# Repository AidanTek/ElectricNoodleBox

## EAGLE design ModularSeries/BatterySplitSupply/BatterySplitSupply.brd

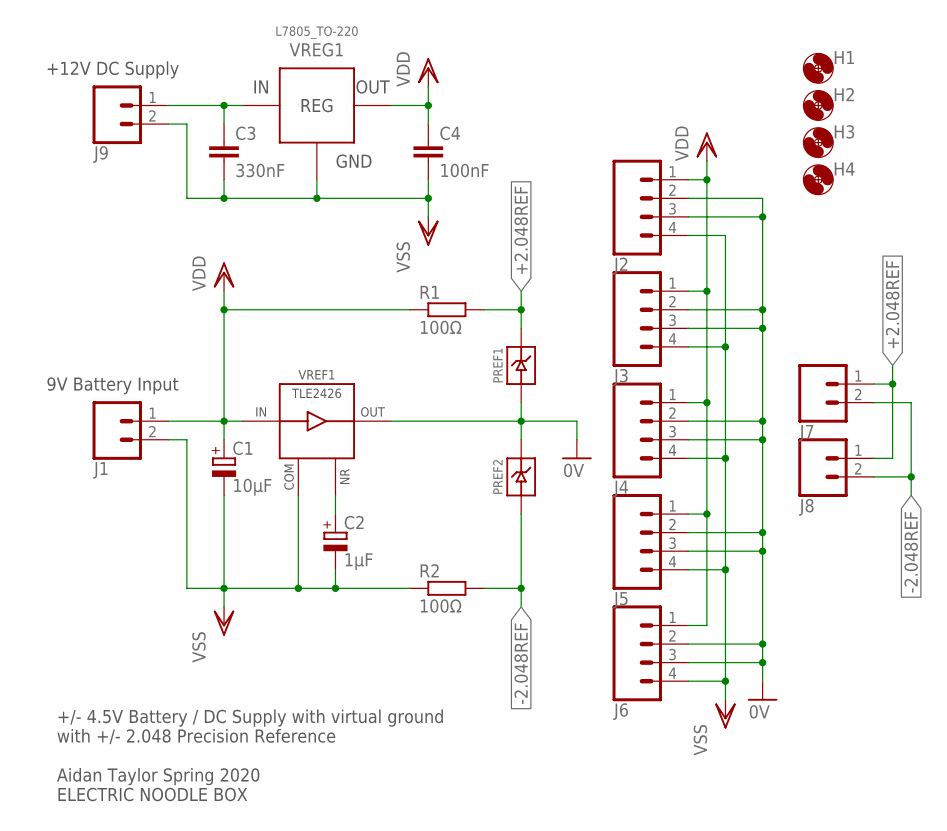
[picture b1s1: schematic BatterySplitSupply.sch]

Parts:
C1: 10µF; E2-5
C2: 1µF; E2-5
C3: 330nF; C050-025X075
C4: 100nF; C050-025X075
H1, H2, H3, H4: MOUNT-HOLE3.2; 3,2
J1, J7, J8, J9: 2XMOLEX; MOLEX-1X2
J2, J3, J4, J5, J6: 4XMOLEX; MOLEX-1X4
PREF1, PREF2: LM4040TH; TO-92
R1, R2: 100Ω; 0207/10
VREF1: TLE2426DIL; DIL08
VREG1: L7805_TO-220; TO220H

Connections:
0V: J2.2, J2.3, J3.2, J3.3, J4.2, J4.3, J5.2, J5.3, J6.2, J6.3, PREF1.3 (ANODE), PREF2.2 (CATHODE), VREF1.1 (OUTPUT)
+2.048REF: J7.1, J8.1, PREF1.2 (CATHODE), R1.2
-2.048REF: J7.2, J8.2, PREF2.3 (ANODE), R2.2
GND: C3.2, C4.2, J9.2, VREG1.2 (GND)
unnamed: C3.1, J9.1, VREG1.1 (VIN)
unnamed: C2.+, VREF1.8 (NR)
VDD: C1.+, C4.1, J1.1, J2.1, J3.1, J4.1, J5.1, J6.1, R1.1, VREF1.3 (INPUT), VREG1.3 (VOUT)
VSS: C1.-, C2.-, J1.2, J2.4, J3.4, J4.4, J5.4, J6.4, R2.1, VREF1.2 (COM)

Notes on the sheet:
+12V DC Supply
9V Battery Input
+/- 4.5V Battery / DC Supply with virtual ground with +/- 2.048 Precision Reference Aidan Taylor Spring 2020 ELECTRIC NOODLE BOX

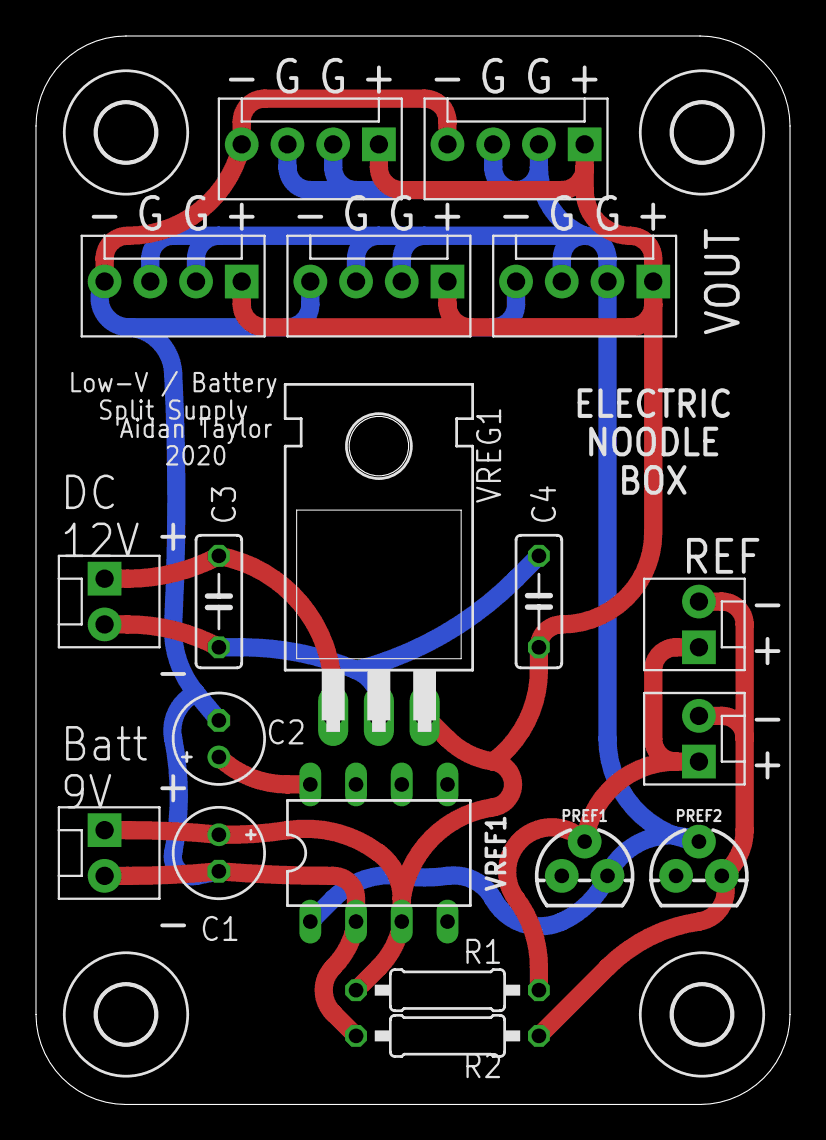
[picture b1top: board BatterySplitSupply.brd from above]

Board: 2 copper layers, 41.9 x 59.4 mm, 23 parts (0 on the bottom side), 8 nets.

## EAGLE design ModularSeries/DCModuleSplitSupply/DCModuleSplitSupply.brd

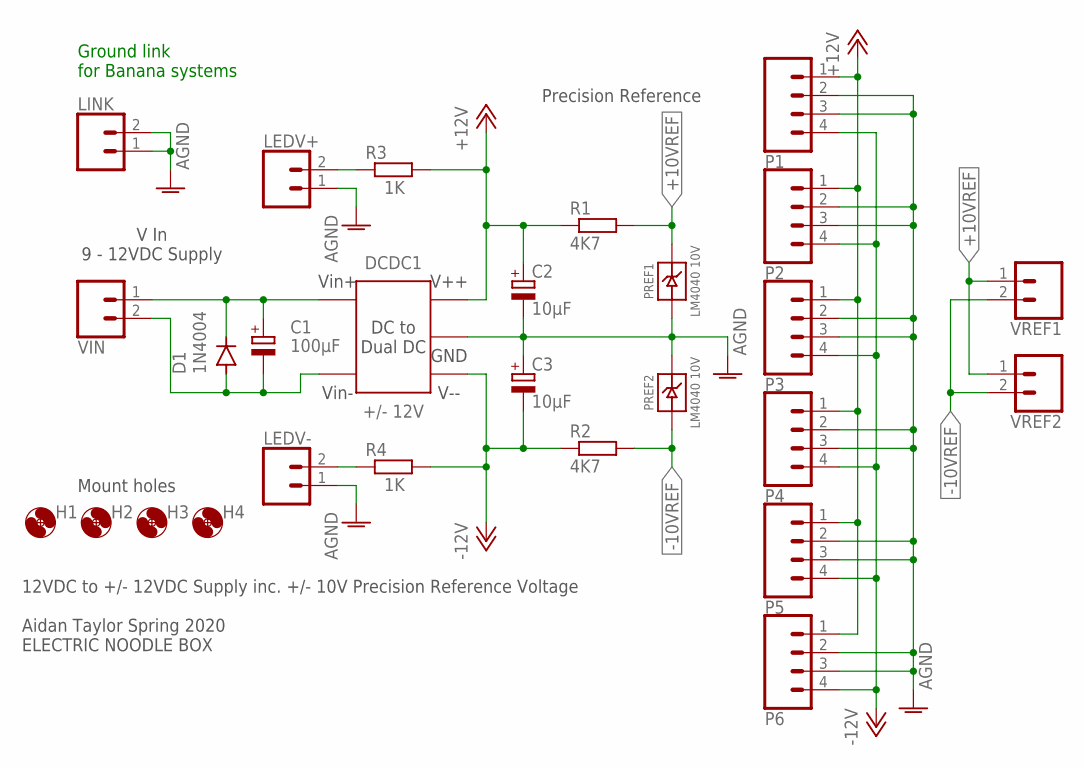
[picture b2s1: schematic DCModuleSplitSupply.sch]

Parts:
C1: 100µF; E2,5-6
C2, C3: 10µF; E2-5
D1: 1N4004; DO41-10
DCDC1: +/- 12V; VRA_ZP-6WR3_SERIES
H1, H2, H3, H4: MOUNT-HOLE3.2; 3,2
LEDV+: 2XWIREPAD; 1X02
LEDV-: 2XWIREPAD; 1X02
LINK: 2XWIREPAD; 1X02
P1, P2, P3, P4, P5, P6: 4XMOLEX; MOLEX-1X4
PREF1, PREF2: LM4040 10V; TO-92
R1, R2: 4K7; 0207/10
R3, R4: 1K; 0207/10
VIN: 2XMOLEX; MOLEX-1X2
VREF1, VREF2: 2XMOLEX; MOLEX-1X2

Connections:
+10VREF: PREF1.2 (CATHODE), R1.2, VREF1.1, VREF2.1
+12V: C2.+, DCDC1.VOUT+, P1.1, P2.1, P3.1, P4.1, P5.1, P6.1, R1.1, R3.2
-10VREF: PREF2.3 (ANODE), R2.2, VREF1.2, VREF2.2
-12V: C3.-, DCDC1.VOUT-, P1.4, P2.4, P3.4, P4.4, P5.4, P6.4, R2.1, R4.2
AGND: C2.-, C3.+, DCDC1.0V, DCDC1.0V2 (0V), LEDV+.1, LEDV-.1, LINK.1, LINK.2, P1.2, P1.3, P2.2, P2.3, P3.2, P3.3, P4.2, P4.3, P5.2, P5.3, P6.2, P6.3, PREF1.3 (ANODE), PREF2.2 (CATHODE)
unnamed: LEDV+.2, R3.1
unnamed: LEDV-.2, R4.1
unnamed: C1.+, D1.C, DCDC1.VIN (VIN+), DCDC1.VIN2 (VIN+), VIN.1
unnamed: C1.-, D1.A, DCDC1.GND (VIN-), DCDC1.GND2 (VIN-), VIN.2

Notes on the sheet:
V In 9 - 12VDC Supply
12VDC to +/- 12VDC Supply inc. +/- 10V Precision Reference Voltage Aidan Taylor Spring 2020 ELECTRIC NOODLE BOX
Precision Reference
Mount holes
Ground link for Banana systems

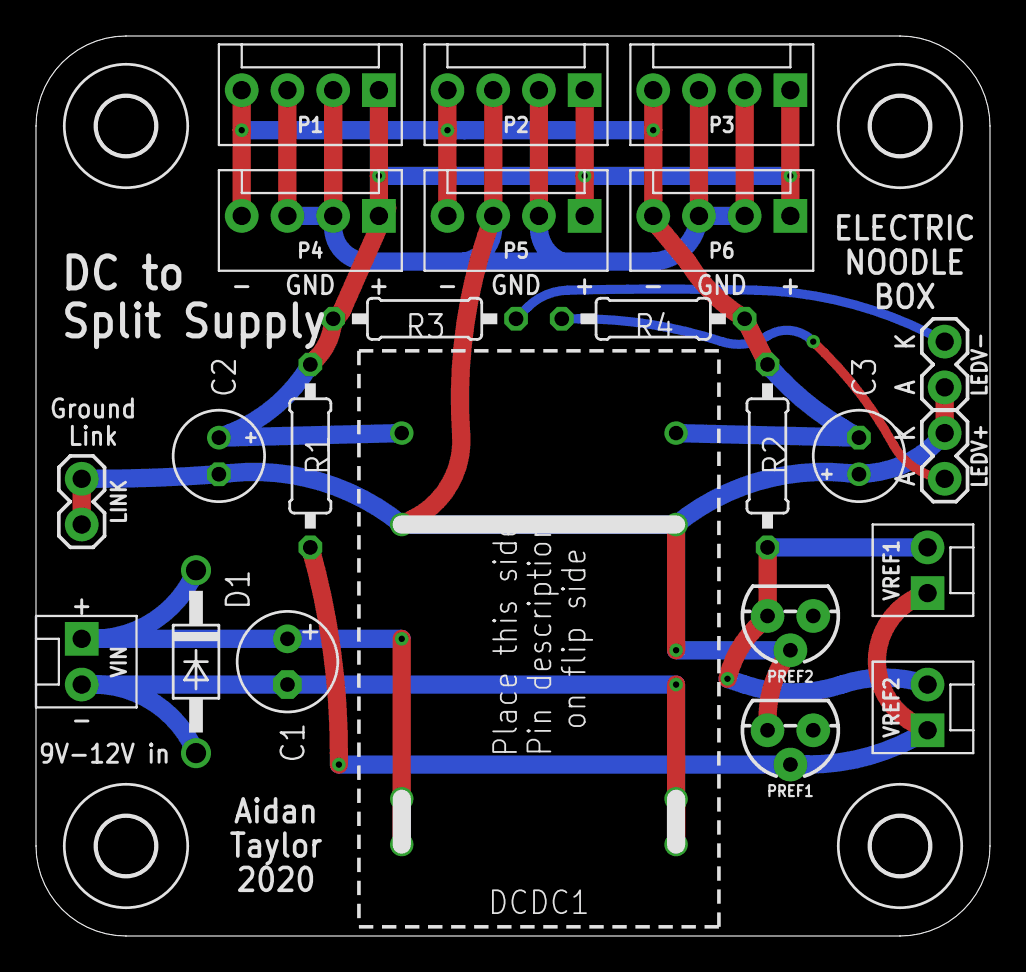
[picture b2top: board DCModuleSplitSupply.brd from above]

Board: 2 copper layers, 53.0 x 50.0 mm, 27 parts (0 on the bottom side), 9 nets.

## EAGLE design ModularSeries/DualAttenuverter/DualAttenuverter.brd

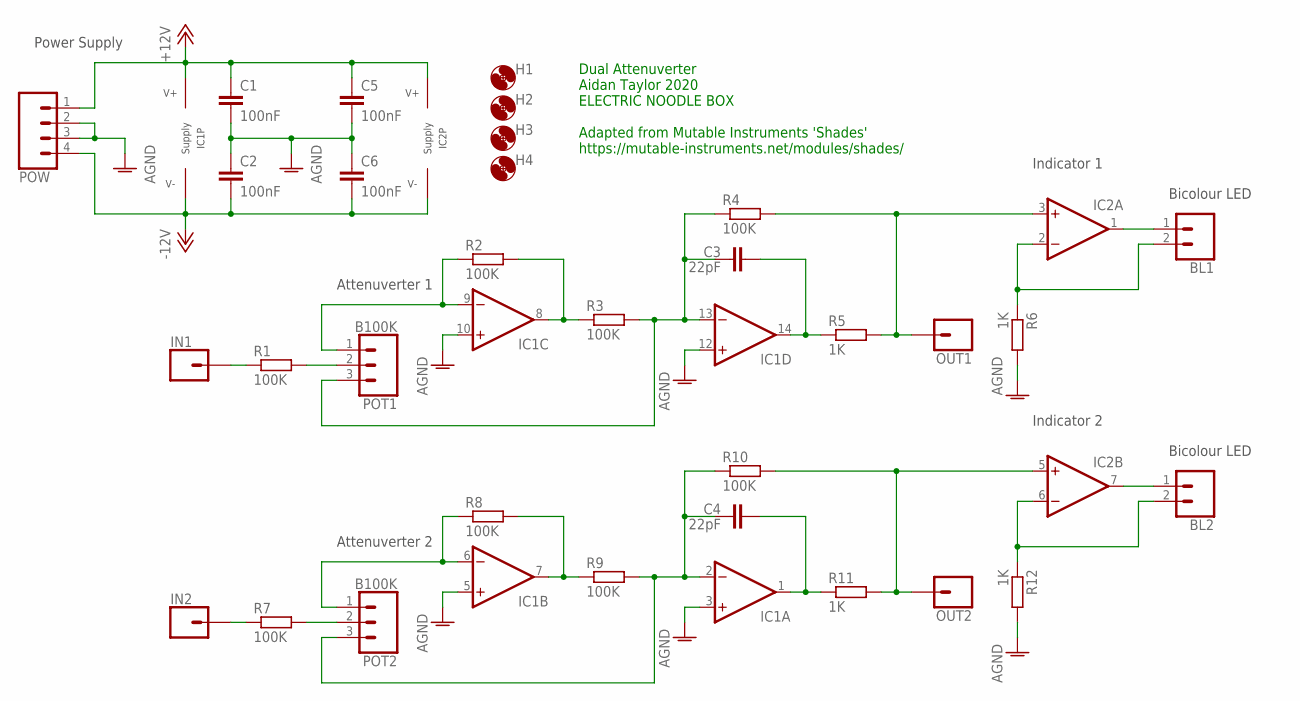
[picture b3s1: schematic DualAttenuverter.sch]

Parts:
BL1, BL2: 2XWIREPAD; 1X02
C1, C2, C5, C6: 100nF; C050-025X075
C3, C4: 22pF; C050-025X075
H1, H2, H3, H4: MOUNT-HOLE3.2; 3,2
IC1: TL0X4DIL; DIL14
IC2: LM358; DIL08
IN1, IN2: 1XWIREPAD; 1X01
OUT1, OUT2: 1XWIREPAD; 1X01
POT1, POT2: B100K; 1X03
POW: 4XMOLEX; MOLEX-1X4
R1, R2, R3, R4, R7, R8, R9, R10: 100K; 0207/10
R5, R6, R11, R12: 1K; 0207/10

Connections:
+12V: C1.1, C5.1, IC1.4 (V+), IC2.8 (V+), POW.1
-12V: C2.2, C6.2, IC1.11 (V-), IC2.4 (V-), POW.4
AGND: C1.2, C2.1, C5.2, C6.1, IC1.3 (+IN), IC1.5 (+IN), IC1.10 (+IN), IC1.12 (+IN), POW.2, POW.3, R6.2, R12.2
unnamed: POT1.2, R1.2
unnamed: IC1.9 (-IN), POT1.1, R2.1
unnamed: POT2.2, R7.2
unnamed: IC1.8 (OUT), R2.2, R3.1
unnamed: C3.1, IC1.13 (-IN), POT1.3, R3.2, R4.1
unnamed: IC2.3 (+IN), OUT1.1, R4.2, R5.2
unnamed: C3.2, IC1.14 (OUT), R5.1
unnamed: BL1.1, IC2.1 (OUT)
unnamed: IN1.1, R1.1
unnamed: IC1.6 (-IN), POT2.1, R8.1
unnamed: IC1.7 (OUT), R8.2, R9.1
unnamed: C4.1, IC1.2 (-IN), POT2.3, R9.2, R10.1
unnamed: IC2.5 (+IN), OUT2.1, R10.2, R11.2
unnamed: C4.2, IC1.1 (OUT), R11.1
unnamed: IN2.1, R7.1
unnamed: BL2.1, IC2.7 (OUT)
unnamed: BL2.2, IC2.6 (-IN), R12.1
unnamed: BL1.2, IC2.2 (-IN), R6.1

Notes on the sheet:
Power Supply
Attenuverter 1
Attenuverter 2
Indicator 1
Indicator 2
Bicolour LED
Dual Attenuverter Aidan Taylor 2020 ELECTRIC NOODLE BOX Adapted from Mutable Instruments 'Shades' https://mutable-instruments.net/modules/shades/

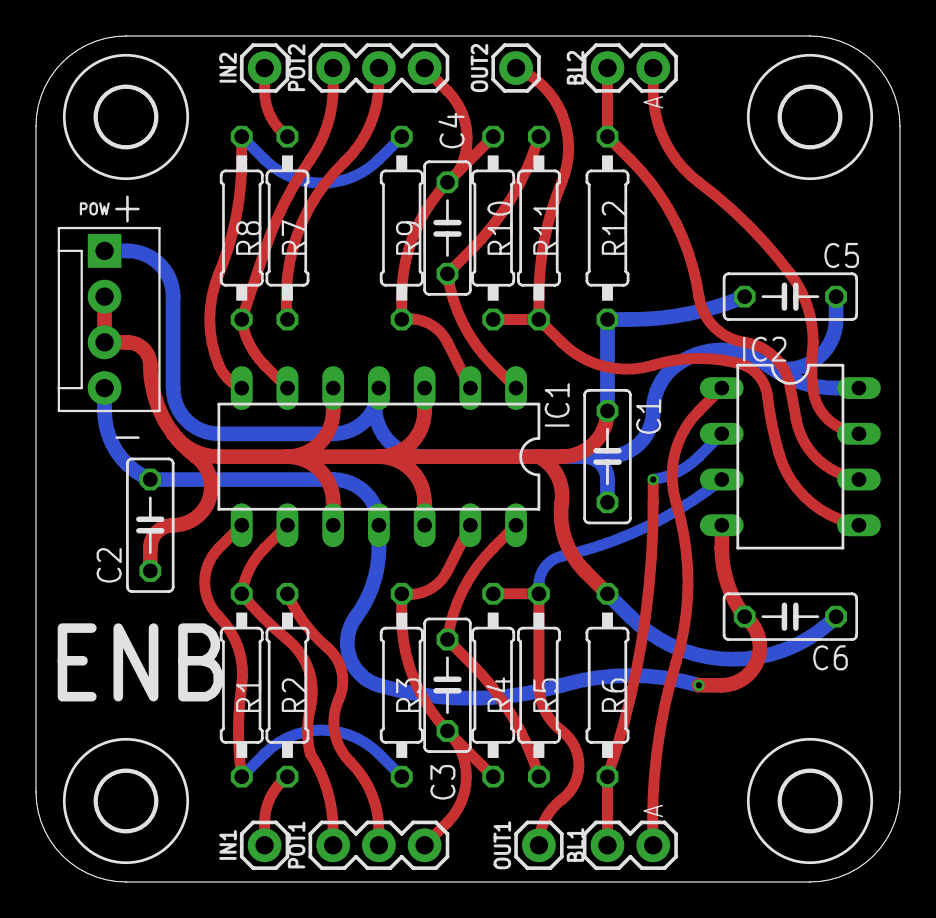
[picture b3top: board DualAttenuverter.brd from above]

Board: 2 copper layers, 48.0 x 47.0 mm, 33 parts (0 on the bottom side), 21 nets.

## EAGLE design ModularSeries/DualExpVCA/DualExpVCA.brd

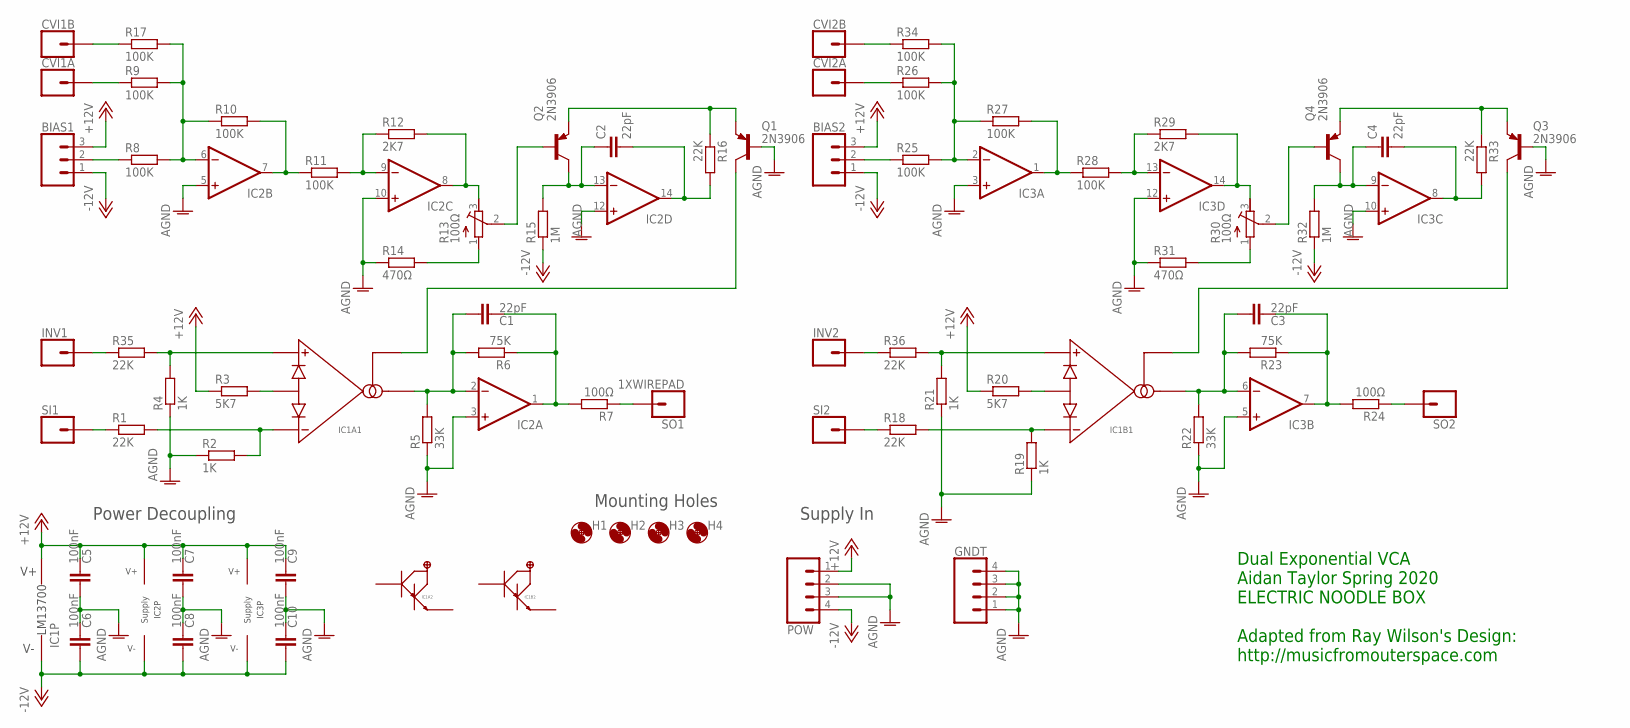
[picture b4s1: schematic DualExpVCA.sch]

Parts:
BIAS1, BIAS2: 3XWIREPAD; 1X03
C1, C2, C3, C4: 22pF; C050-025X075
C5, C6, C7, C8, C9, C10: 100nF; C050-025X075
CVI1A, CVI1B, CVI2A, CVI2B: 1XWIREPAD; 1X01
GNDT: 4XWIREPAD; 1X04
H1, H2, H3, H4: MOUNT-HOLE3.2; 3,2
IC1: LM13700_DIP; DIL16
IC2, IC3: TL0X4_DIP; DIL14
INV1, INV2: 1XWIREPAD; 1X01
POW: 4XMOLEX; MOLEX-1X4
Q1, Q2, Q3, Q4: 2N3906; TO92
R1, R16, R18, R33, R35, R36: 22K; 0207/10
R2, R4, R19, R21: 1K; 0207/10
R3, R20: 5K7; 0207/10
R5, R22: 33K; 0207/10
R6, R23: 75K; 0207/10
R7, R24: 100Ω; 0207/10
R8, R9, R10, R11, R17, R25, R26, R27, R28, R34: 100K; 0207/10
R12, R29: 2K7; 0207/10
R13, R30: 100Ω; RTRIM3296W
R14, R31: 470Ω; 0207/10
R15, R32: 1M; 0207/10
SI1, SI2: 1XWIREPAD; 1X01
SO1, SO2: 1XWIREPAD; 1X01

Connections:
+12V: BIAS1.3, BIAS2.3, C5.2, C7.2, C9.2, IC1.11 (V+), IC2.4 (V+), IC3.4 (V+), POW.1, R3.1, R20.1
-12V: BIAS1.1, BIAS2.1, C6.1, C8.1, C10.1, IC1.6 (V-), IC2.11 (V-), IC3.11 (V-), POW.4, R15.1, R32.1
AGND: C5.1, C6.2, C7.1, C8.2, C9.1, C10.2, GNDT.1, GNDT.2, GNDT.3, GNDT.4, IC2.3 (+IN), IC2.5 (+IN), IC2.10 (+IN), IC2.12 (+IN), IC3.3 (+IN), IC3.5 (+IN), IC3.10 (+IN), IC3.12 (+IN), POW.2, POW.3, Q1.2 (B), Q3.2 (B), R2.1, R4.1, R5.1, R14.1, R19.1, R21.1, R22.1, R31.1
unnamed: R1.1, SI1.1
unnamed: IC1.3 (AMP+), R4.2, R35.2
unnamed: BIAS1.2, R8.1
unnamed: IC1.4 (AMP-), R1.2, R2.2
unnamed: IC1.2 (DIODES), R3.2
unnamed: R7.1, SO1.1
unnamed: C1.1, IC1.5 (AMPOUT), IC2.2 (-IN), R5.2, R6.2
unnamed: C1.2, IC2.1 (OUT), R6.1, R7.2
unnamed: CVI1A.1, R9.1
unnamed: IC2.6 (-IN), R8.2, R9.2, R10.1, R17.2
unnamed: IC2.7 (OUT), R10.2, R11.1
unnamed: IC2.9 (-IN), R11.2, R12.1
unnamed: IC2.8 (OUT), R12.2, R13.3 (E)
unnamed: R13.1 (A), R14.2
unnamed: Q2.2 (B), R13.2 (S)
unnamed: C2.1, IC2.13 (-IN), Q2.1 (C), R15.2
unnamed: Q1.3 (E), Q2.3 (E), R16.1
unnamed: C2.2, IC2.14 (OUT), R16.2
unnamed: CVI1B.1, R17.1
unnamed: IC1.1 (AMPBIAS), Q1.1 (C)
unnamed: R18.1, SI2.1
unnamed: IC1.14 (AMP+), R21.2, R36.2
unnamed: IC1.13 (AMP-), R18.2, R19.2
unnamed: IC1.15 (DIODES), R20.2
unnamed: C3.1, IC1.12 (AMPOUT), IC3.6 (-IN), R22.2, R23.2
unnamed: C3.2, IC3.7 (OUT), R23.1, R24.2
unnamed: R24.1, SO2.1
unnamed: BIAS2.2, R25.1
unnamed: CVI2A.1, R26.1
unnamed: IC3.2 (-IN), R25.2, R26.2, R27.1, R34.2
unnamed: IC3.1 (OUT), R27.2, R28.1
unnamed: IC3.13 (-IN), R28.2, R29.1
unnamed: IC3.14 (OUT), R29.2, R30.3 (E)
unnamed: R30.1 (A), R31.2
unnamed: C4.1, IC3.9 (-IN), Q4.1 (C), R32.2
unnamed: C4.2, IC3.8 (OUT), R33.2
unnamed: Q3.3 (E), Q4.3 (E), R33.1
unnamed: IC1.16 (AMPBIAS), Q3.1 (C)
unnamed: Q4.2 (B), R30.2 (S)
unnamed: CVI2B.1, R34.1
unnamed: INV1.1, R35.1
unnamed: INV2.1, R36.1

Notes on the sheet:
Dual Exponential VCA Aidan Taylor Spring 2020 ELECTRIC NOODLE BOX Adapted from Ray Wilson's Design: http://musicfromouterspace.com
Mounting Holes
Power Decoupling
Supply In

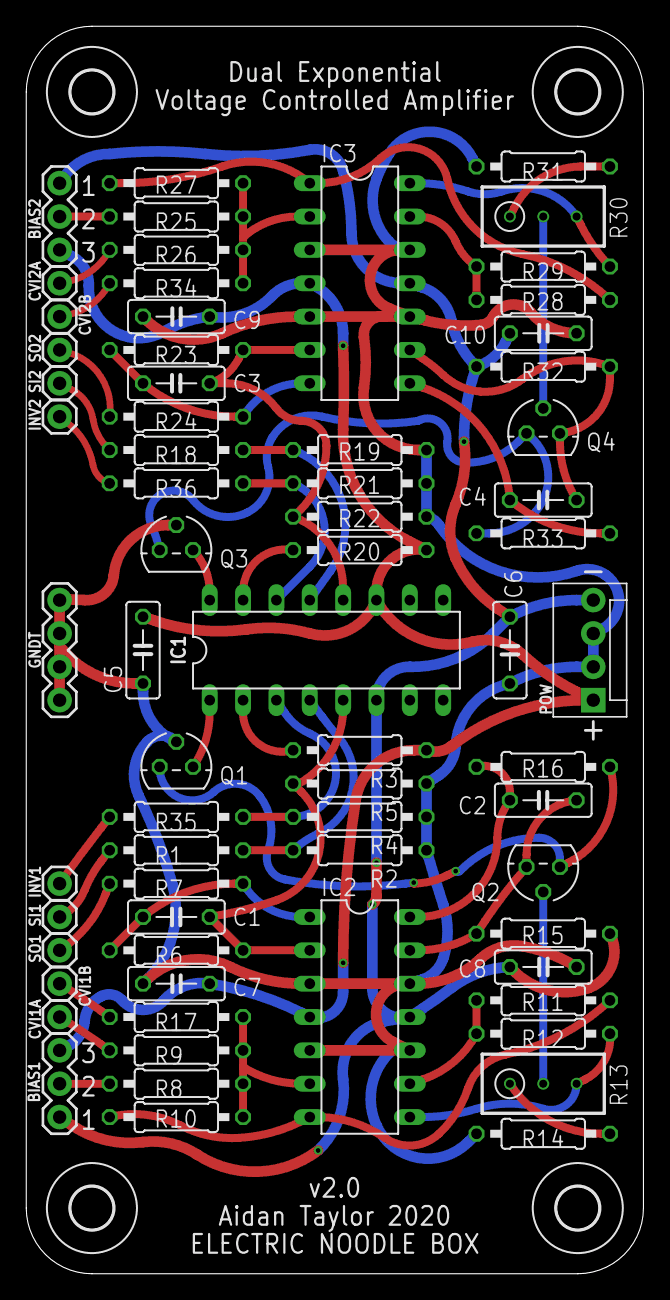
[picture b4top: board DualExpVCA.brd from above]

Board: 2 copper layers, 47.0 x 95.0 mm, 71 parts (0 on the bottom side), 45 nets.

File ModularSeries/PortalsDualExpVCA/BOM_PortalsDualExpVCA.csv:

Qty,Value,Package,Parts,Description,Retailer,Catalogue
,,,,,,
10,100K,0207/10,"R8, R9, R10, R11, R17, R25, R26, R27, R28, R34",RESISTOR 1/4W,Farnell,2329853
2,100Ω,0207/10,"R7, R24",RESISTOR 1/4W,Farnell,2329854
4,1K,0207/10,"R2, R4, R19, R21",RESISTOR 1/4W,Farnell,2329885
2,1M,0207/10,"R15, R32",RESISTOR 1/4W,Farnell,2329894
6,22K,0207/10,"R1, R16, R18, R33, R35, R36",RESISTOR 1/4W,Farnell,2329901
2,2K7,0207/10,"R12, R29",RESISTOR 1/4W,Farnell,2329914
2,33K,0207/10,"R5, R22",RESISTOR 1/4W,Farnell,2329922
2,470Ω,0207/10,"R14, R31",RESISTOR 1/4W,Farnell,2329942
2,5K6,0207/10,"R3, R20",RESISTOR 1/4W,Farnell,2329958
2,75K,0207/10,"R6, R23",RESISTOR 1/4W,Farnell,2329972
2,100Ω,RTRIM3296W,"R13, R30",Trimm resistor,Farnell,9353186
,,,,,,
6,100nF,C050-025X075,"C5, C6, C7, C8, C9, C10",CAPACITOR,Farnell,2797801
4,22pF,C050-025X075,"C1, C2, C3, C4",CAPACITOR,Farnell,1457695
,,,,,,
4,2N3906,TO92,"Q1, Q2, Q3, Q4",PNP Transistor,Farnell,1574372
1,LM13700_DIP,DIL16,IC1,LM13700 16 pin DIL,Farnell,3118206
2,TL084_DIP,DIL14,"IC2, IC3",TL084 14 pin DIL,Farnell,3005140
,,,,,,
1,4XMOLEX,MOLEX-1X4,POW,Molex 4 pin KK 254 6373 series,Farnell,1462920
,,,,,,
10,Banana Connector,,"CVI1A, CVI1B, CVI2A, CVI2B, INV1, INV2, SI1, SI2, SO1, SO2",Banana or Jack patch point (panel part),Farnell,1698951
2,B100K,,"BIAS1, BIAS2",Taiwan Alpha 16mm (panel part),Rapid,65-0756
4,B10K,,"CVI1A, CVI1B, CVI2A, CVI2B",Taiwan Alpha 16mm (panel part),Rapid,65-0753
2,SPDT,,"INV1, INV2, SI1, SI2", SPDT Toggle Switch, Farnell, 9473416

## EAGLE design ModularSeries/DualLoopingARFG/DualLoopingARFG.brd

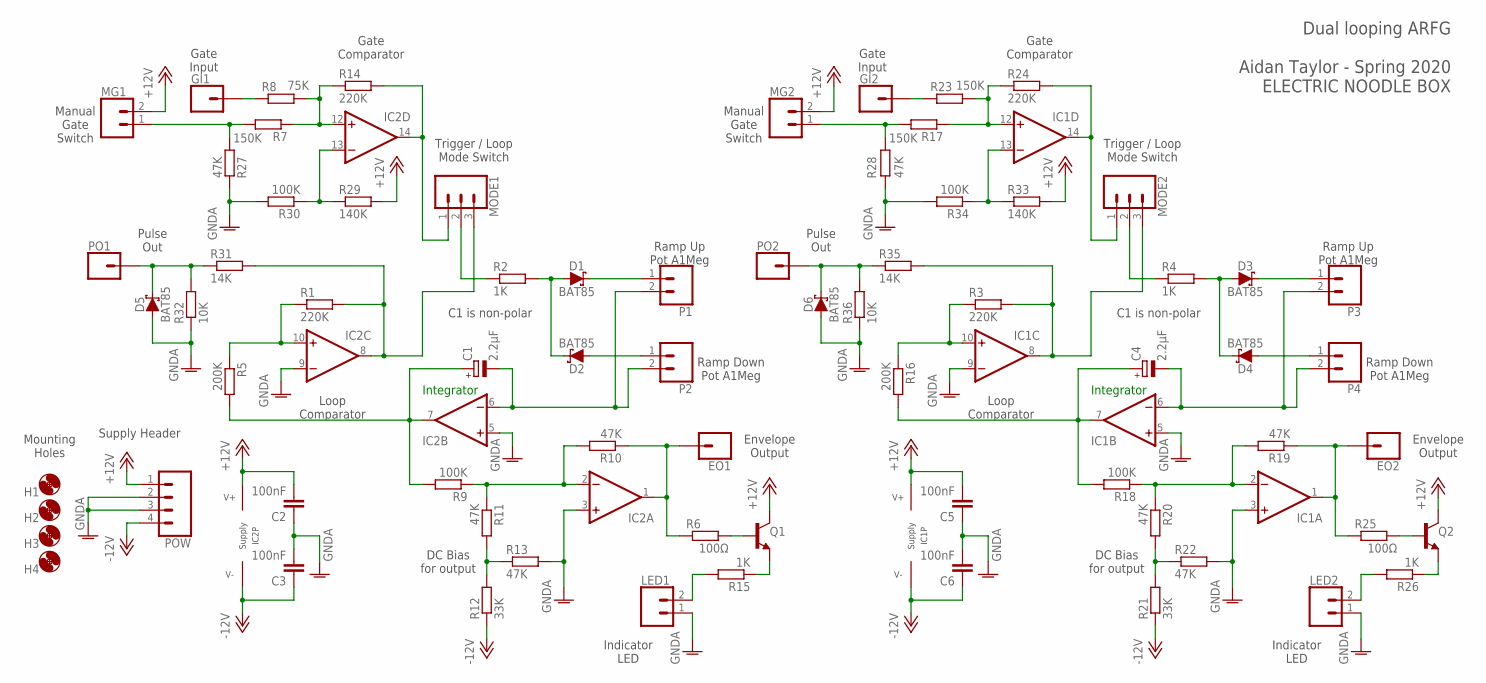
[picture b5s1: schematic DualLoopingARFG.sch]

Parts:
C1, C4: 2.2µF; E2-5
C2, C3, C5, C6: 100nF; C050-025X075
D1, D2, D3, D4, D5, D6: BAT85; DO35-7
EO1, EO2: 1XWIREPAD; 1X01
GI1, GI2: 1XWIREPAD; 1X01
H1, H2, H3, H4: MOUNT-HOLE3.2; 3,2
IC1, IC2: TL0X4DIL; DIL14
LED1, LED2: 2XWIREPAD; 1X02
MG1, MG2: 2XWIREPAD; 1X02
MODE1, MODE2: 3XWIREPAD; 1X03
P1, P2, P3, P4: 2XWIREPAD; 1X02
PO1, PO2: 1XWIREPAD; 1X01
POW: 4XMOLEX; MOLEX-1X4
Q1, Q2: 2N3904; TO92
R1, R3, R14, R24: 220K; 0207/10
R2, R4, R15, R26: 1K; 0207/10
R5, R16: 200K; 0207/10
R6, R25: 100Ω; 0207/10
R7, R17, R23: 150K; 0207/10
R8: 75K; 0207/10
R9, R18, R30, R34: 100K; 0207/10
R10, R11, R13, R19, R20, R22, R27, R28: 47K; 0207/10
R12, R21: 33K; 0207/10
R29, R33: 140K; 0207/10
R31, R35: 14K; 0207/10
R32, R36: 10K; 0207/10

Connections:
+12V: C2.2, C5.2, IC1.4 (V+), IC2.4 (V+), MG1.2, MG2.2, POW.1, Q1.1 (C), Q2.1 (C), R29.2, R33.2
-12V: C3.1, C6.1, IC1.11 (V-), IC2.11 (V-), POW.4, R12.1, R21.1
ENV1_TRIG: GI1.1, R8.1
ENV1_TRIG1: GI2.1, R23.1
ENVELOPE_OUTPUT: EO1.1, IC2.1 (OUT), R6.1, R10.1
ENVELOPE_OUTPUT1: EO2.1, IC1.1 (OUT), R19.1, R25.1
GNDA: C2.1, C3.2, C5.1, C6.2, D5.A, D6.A, IC1.3 (+IN), IC1.5 (+IN), IC1.9 (-IN), IC2.3 (+IN), IC2.5 (+IN), IC2.9 (-IN), LED1.1, LED2.1, POW.2, POW.3, R13.2, R22.2, R27.2, R28.2, R30.2, R32.1, R34.2, R36.1
unnamed: IC2.8 (OUT), MODE1.3, R1.2, R31.2
unnamed: D1.A, D2.C, R2.2
unnamed: D1.C, P1.1
unnamed: D2.A, P2.1
unnamed: C1.-, IC2.6 (-IN), P1.2, P2.2
unnamed: Q1.2 (B), R6.2
unnamed: C1.+, IC2.7 (OUT), R5.2, R9.2
unnamed: IC2.10 (+IN), R1.1, R5.1
unnamed: IC2.2 (-IN), R9.1, R10.2, R11.1
unnamed: Q1.3 (E), R15.1
unnamed: R11.2, R12.2, R13.1
unnamed: MG1.1, R7.2, R27.1
unnamed: IC2.12 (+IN), R7.1, R8.2, R14.1
unnamed: MODE1.2, R2.1
unnamed: IC2.14 (OUT), MODE1.1, R14.2
unnamed: LED1.2, R15.2
unnamed: IC1.8 (OUT), MODE2.3, R3.2, R35.2
unnamed: D3.A, D4.C, R4.2
unnamed: D4.A, P4.1
unnamed: C4.-, IC1.6 (-IN), P3.2, P4.2
unnamed: C4.+, IC1.7 (OUT), R16.2, R18.2
unnamed: IC1.10 (+IN), R3.1, R16.1
unnamed: IC1.2 (-IN), R18.1, R19.2, R20.1
unnamed: R20.2, R21.2, R22.1
unnamed: MG2.1, R17.2, R28.1
unnamed: IC1.12 (+IN), R17.1, R23.2, R24.1
unnamed: IC1.14 (OUT), MODE2.1, R24.2
unnamed: MODE2.2, R4.1
unnamed: Q2.2 (B), R25.2
unnamed: Q2.3 (E), R26.1
unnamed: LED2.2, R26.2
unnamed: D3.C, P3.1
unnamed: IC2.13 (-IN), R29.1, R30.1
unnamed: D5.C, PO1.1, R31.1, R32.2
unnamed: IC1.13 (-IN), R33.1, R34.1
unnamed: D6.C, PO2.1, R35.1, R36.2

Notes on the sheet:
DC Bias for output
Integrator
Gate Comparator
Loop Comparator
Trigger / Loop Mode Switch
C1 is non-polar
Ramp Up Pot A1Meg
Ramp Down Pot A1Meg
Indicator LED
Manual Gate Switch
Gate Input
Envelope Output
Dual looping ARFG Aidan Taylor - Spring 2020 ELECTRIC NOODLE BOX
Supply Header
Mounting Holes
Pulse Out

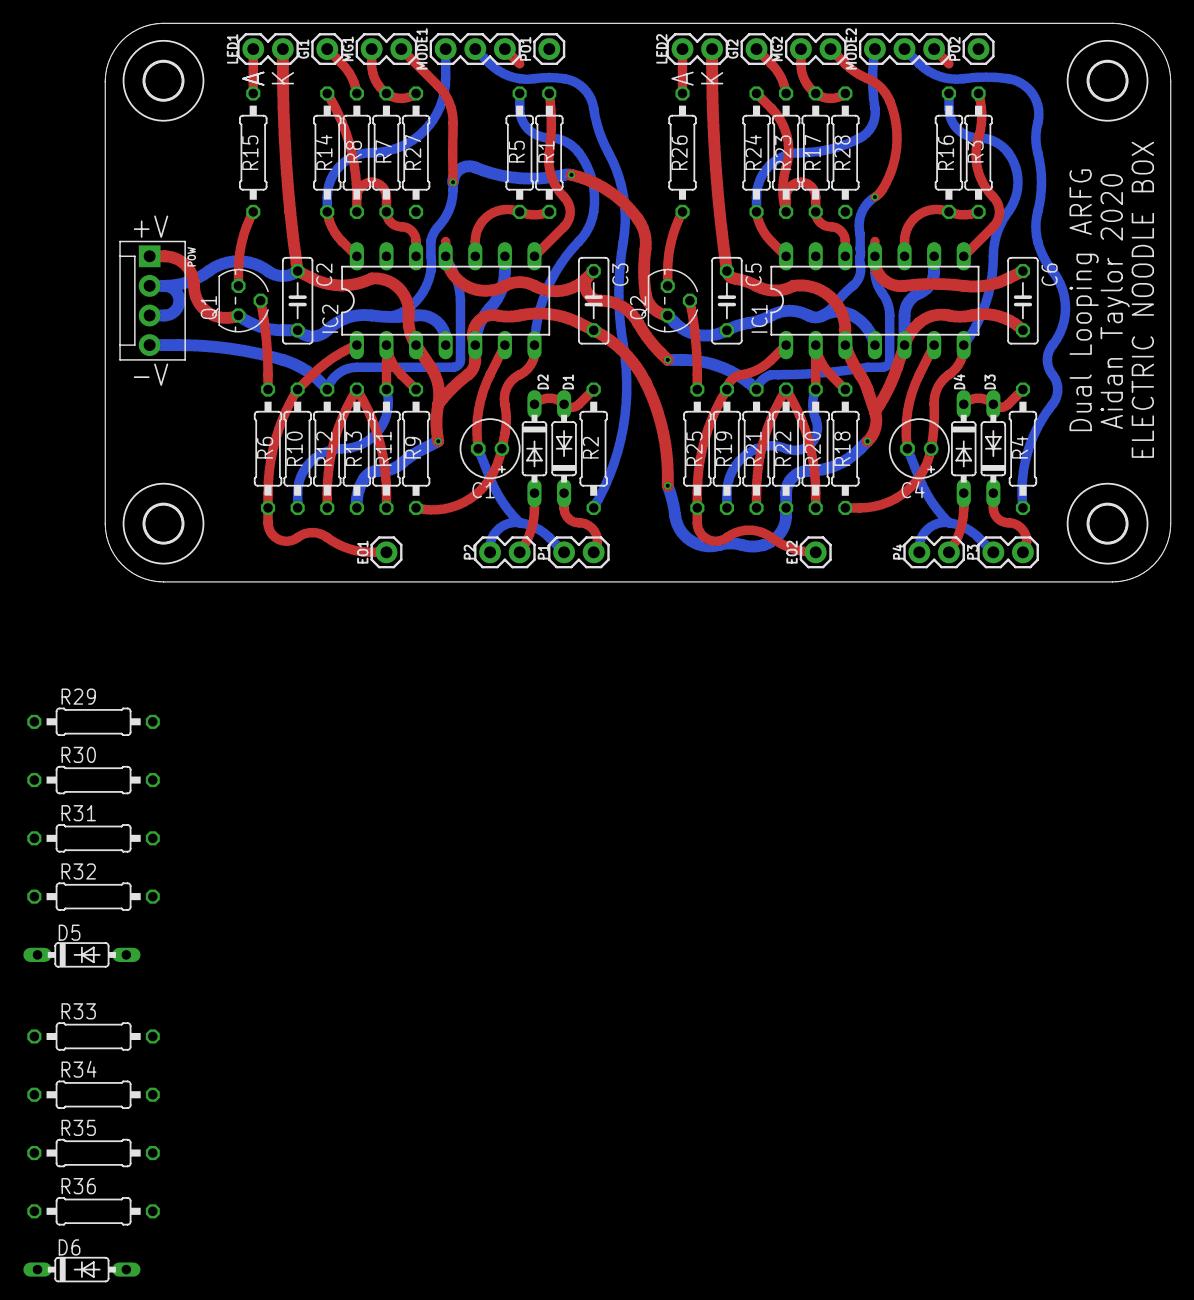
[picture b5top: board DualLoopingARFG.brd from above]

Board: 2 copper layers, 91.4 x 47.9 mm, 73 parts (0 on the bottom side), 43 nets.

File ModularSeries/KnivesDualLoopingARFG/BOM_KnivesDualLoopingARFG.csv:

Qty,Value,Package,Parts,Description,Retailer,Catalogue
,,,,,,
4,100K,0207/10,"R9, R18, R30, R34",RESISTOR 1/4W,Farnell,2329853
2,100Ω,0207/10,"R6, R25",RESISTOR 1/4W,Farnell,2329854
2,10K,0207/10,"R32, R36",RESISTOR 1/4W,Farnell,2329855
2,140K,0207/10,"R29, R33",RESISTOR 1/4W,Farnell,1083485
2,14K,0207/10,"R31, R35",RESISTOR 1/4W,Farnell,1563095
3,150K,0207/10,"R7, R17, R23",RESISTOR 1/4W,Farnell,2329871
4,1K,0207/10,"R2, R4, R15, R26",RESISTOR 1/4W,Farnell,2329885
2,200K,0207/10,"R5, R16",RESISTOR 1/4W,Farnell,2329895
4,220K,0207/10,"R1, R3, R14, R24",RESISTOR 1/4W,Farnell,2329899
2,33K,0207/10,"R12, R21",RESISTOR 1/4W,Farnell,2329922
8,47K,0207/10,"R10, R11, R13, R19, R20, R22, R27, R28",RESISTOR 1/4W,Farnell,2329944
1,75K,0207/10,R8,RESISTOR 1/4W,Farnell,2329972
,,,,,,
4,100nF,C050-025X075,"C2, C3, C5, C6",CAPACITOR,Farnell,2797801
2,2.2¬µF,E2-5,"C1, C4",CAPACITOR Non-polarised electrolytic ,Farnell,1236667
,,,,,,
6,BAT85,DO35-7,"D1, D2, D3, D4, D5, D6",BAT85 Schottky Diode,Farnell,2889133
2,2N3904,TO92,"Q1, Q2",NPN TRANSISTOR,Farnell,1574370
2,TL084_DIP,DIL14,"IC1, IC2",TL084 14 pin DIL,Farnell,3005140
,,,,,,
6,Banana Connector,,"EO1, EO2, GI1, GI2, PO1, PO2",Banana or Jack patch point (panel part),Farnell,1698951
2,LED,,"LED1, LED2",LED (panel part),Farnell,1581143
2,Push button,,"MG1, MG2",Momentary push button (panel part),Farnell ,1634691
4,A100K,,"P1, P2, P3, P4",Taiwan Alpha 16mm (panel part),Rapid,65-0845
2,SPDT Switch,,"MODE1, MODE2",Toggle switch SPDT (panel part),Farnell,9473491
1,Power Header,,WP1,4 way MTA156 or 10 way IDC,Farnell ,589068

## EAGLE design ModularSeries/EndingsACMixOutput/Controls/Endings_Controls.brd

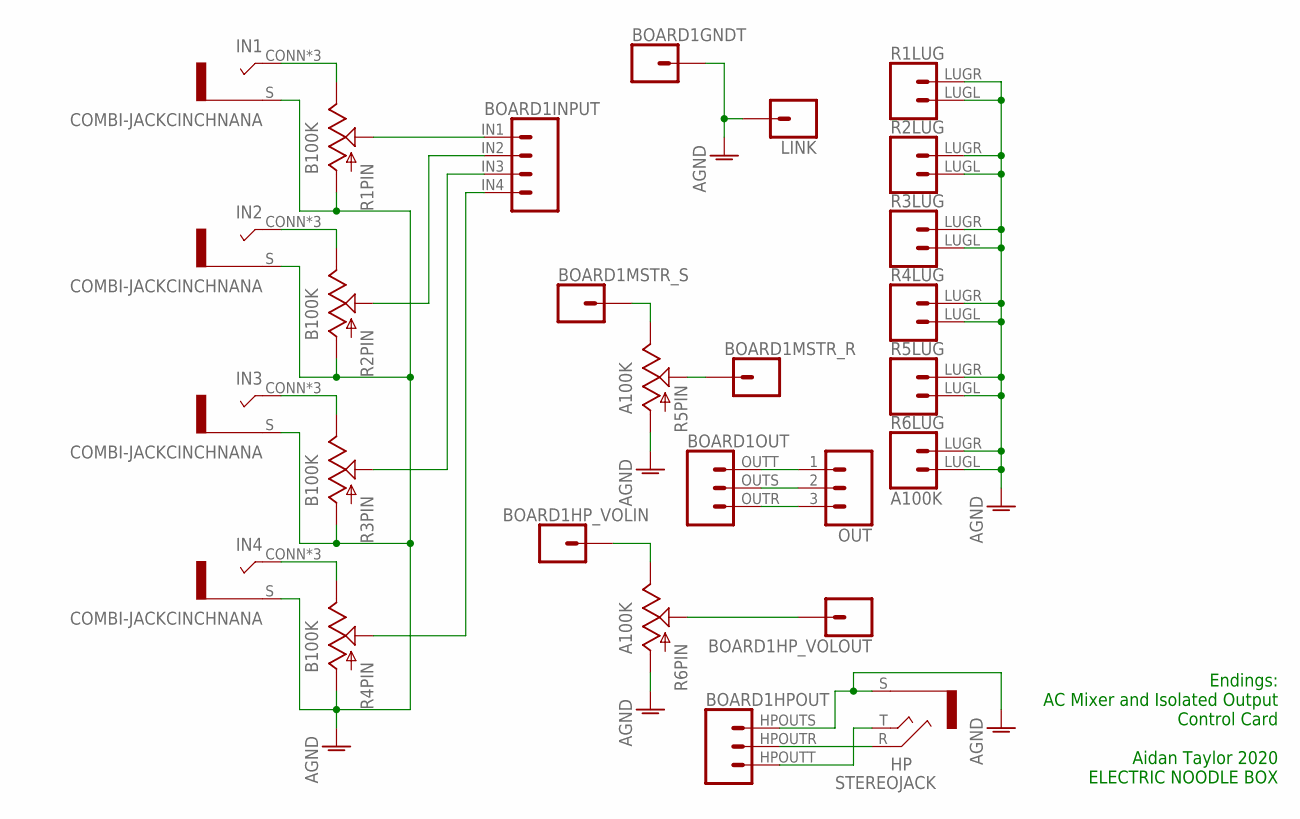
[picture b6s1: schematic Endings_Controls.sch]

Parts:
BOARD1: ENDINGS_LINK; ENDINGS
HP: STEREOJACK; STEREO_JACK_PANEL
IN1, IN2, IN3, IN4: COMBI-JACKCINCHNANA; NEWCOMBOJACK_PANEL
LINK: BANANA_PANEL; CINCHNANA_PANEL
OUT: 3XWIREPAD; 1X03
R1, R2, R3, R4: B100K; ALPHA_RV09_9MMPOT
R5, R6: A100K; ALPHA_RV09_9MMPOT

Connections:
AGND: BOARD1.GND1 (1), BOARD1.GND2 (1), BOARD1.GND3 (1), BOARD1.GND4 (1), BOARD1.HPOUTS (3), HP.S, IN1.S, IN2.S, IN3.S, IN4.S, LINK.CONN, R1.C1 (A), R1.LUGL (1), R1.LUGR (2), R2.C1 (A), R2.LUGL (1), R2.LUGR (2), R3.C1 (A), R3.LUGL (1), R3.LUGR (2), R4.C1 (A), R4.LUGL (1), R4.LUGR (2), R5.C1 (A), R5.LUGL (1), R5.LUGR (2), R6.C1 (A), R6.LUGL (1), R6.LUGR (2)
unnamed: IN1.CONN (T), IN1.T1 (T), IN1.T2 (T), R1.C3 (B)
unnamed: IN2.CONN (T), IN2.T1 (T), IN2.T2 (T), R2.C3 (B)
unnamed: IN3.CONN (T), IN3.T1 (T), IN3.T2 (T), R3.C3 (B)
unnamed: IN4.CONN (T), IN4.T1 (T), IN4.T2 (T), R4.C3 (B)
unnamed: BOARD1.IN1 (1), R1.C2 (W)
unnamed: BOARD1.IN2 (2), R2.C2 (W)
unnamed: BOARD1.IN3 (3), R3.C2 (W)
unnamed: BOARD1.IN4 (4), R4.C2 (W)
unnamed: BOARD1.MSTRVOLOUT (1), R5.C3 (B)
unnamed: BOARD1.MSTRVOLIN (1), R5.C2 (W)
unnamed: BOARD1.HPVOLIN (1), R6.C3 (B)
unnamed: BOARD1.HPVOLOUT (1), R6.C2 (W)
unnamed: BOARD1.OUTT (3), OUT.1
unnamed: BOARD1.OUTS (2), OUT.2
unnamed: BOARD1.OUTR (1), OUT.3
unnamed: BOARD1.HPOUTR (2), HP.R
unnamed: BOARD1.HPOUTT (1), HP.T

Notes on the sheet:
Endings: AC Mixer and Isolated Output Control Card Aidan Taylor 2020 ELECTRIC NOODLE BOX

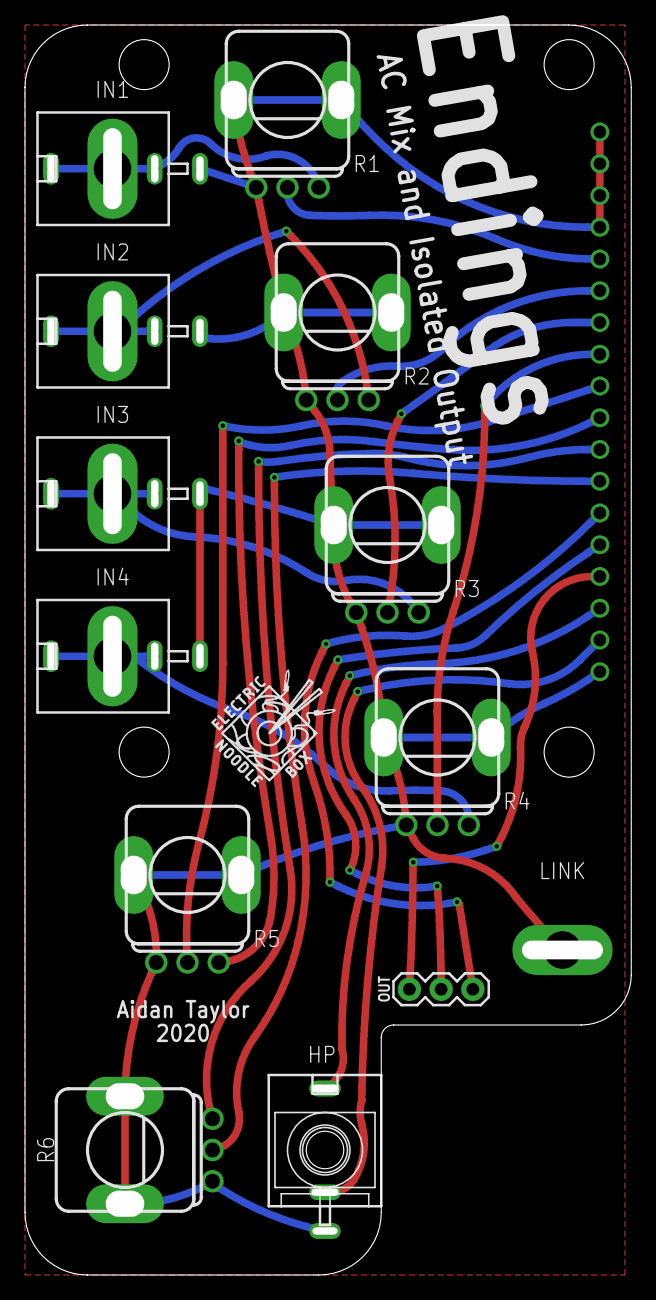
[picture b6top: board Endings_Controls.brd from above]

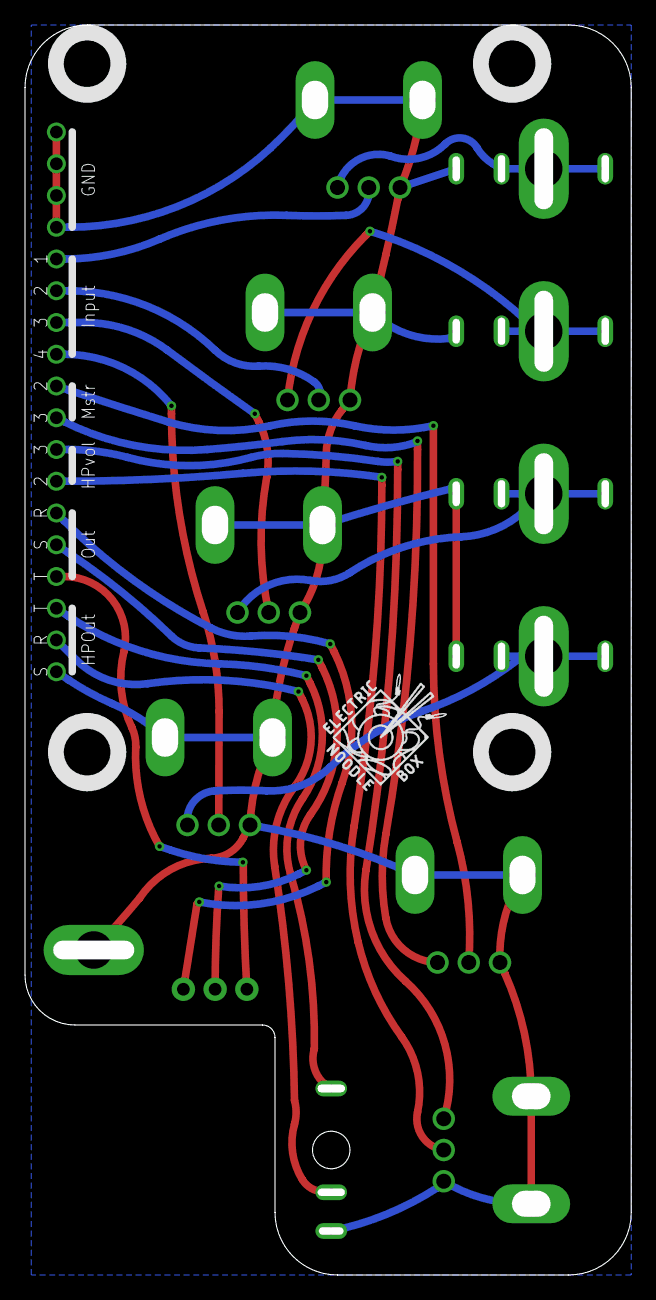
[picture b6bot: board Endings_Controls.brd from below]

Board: 2 copper layers, 48.5 x 100.0 mm, 16 parts (2 on the bottom side), 18 nets.

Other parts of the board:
U$1, U$2: LOGO10X10

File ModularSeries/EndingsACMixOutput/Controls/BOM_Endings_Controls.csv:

Qty,Value,Package,Parts,Description,Retailer,Catalogue
1,"TRS 1/4"" Jack",1X03,OUT,Neutrik Stereo Jack (wired),Farnell,4169190
2,A100K,ALPHA_RV09_9MMPOT,"R5, R6",Taiwan Alpha 9mm Potentiometer,Thonk,D-shaft A100K
4,B100K,ALPHA_RV09_9MMPOT,"R1, R2, R3, R4",Taiwan Alpha 9mm Potentiometer,Thonk,D-shaft B100K
4,Small Knob,Small Knob,"R1, R2, R3, R4",SIFAM/SELCO Small Black,Thonk,Small Black
2,Large Knob,Large Knob,"R5, R6",SIFAM/SELCO Large Black,Thonk,Large Black
4,Small Orange Cap,Small Orange Cap,"R1, R2, R3, R4",SIFAM/SELCO Cap Small Orange,Thonk,Cap Orange Small
2,Large Orange Cap,Large Orange Cap,"R5, R6",SIFAM/SELCO Cap Large Orange,Thonk,Cap Orange Large
1,Black Banana,BANANA_PANEL,LINK,(optional) Johnson/Cinch Banana Black ,Mouser,530-108-0903-1
4,COMBI-JACK,COMBOJACK_PANEL,"IN1, IN2, IN3, IN4",Johnson/Cinch Banana Orange,Mouser,530-108-0906-1
4,COMBI-JACK,COMBOJACK_PANEL,"IN1, IN2, IN3, IN4",(Alternative to above) PJ398SM mini-jack,Thonk,PJ398SM
1,STEREOJACK,STEREO_JACK_PANEL,HP,Stereo Minijack PJ366ST,Thonk,PJ366ST
3,Male Header,Male Header,,8way 1row 2.54mm Header Male,Farnell,2856626
3,Female Header,Female Header,,8way 1row 2.54mm Header Female,Farnell,1668208
4,M3 Standoff,M3 Standoff,,8mm Standoff Nylon,Farnell,1466945
4,M3 Screw,M3 Screw,,Stainless Steel M3,Farnell,1420032
